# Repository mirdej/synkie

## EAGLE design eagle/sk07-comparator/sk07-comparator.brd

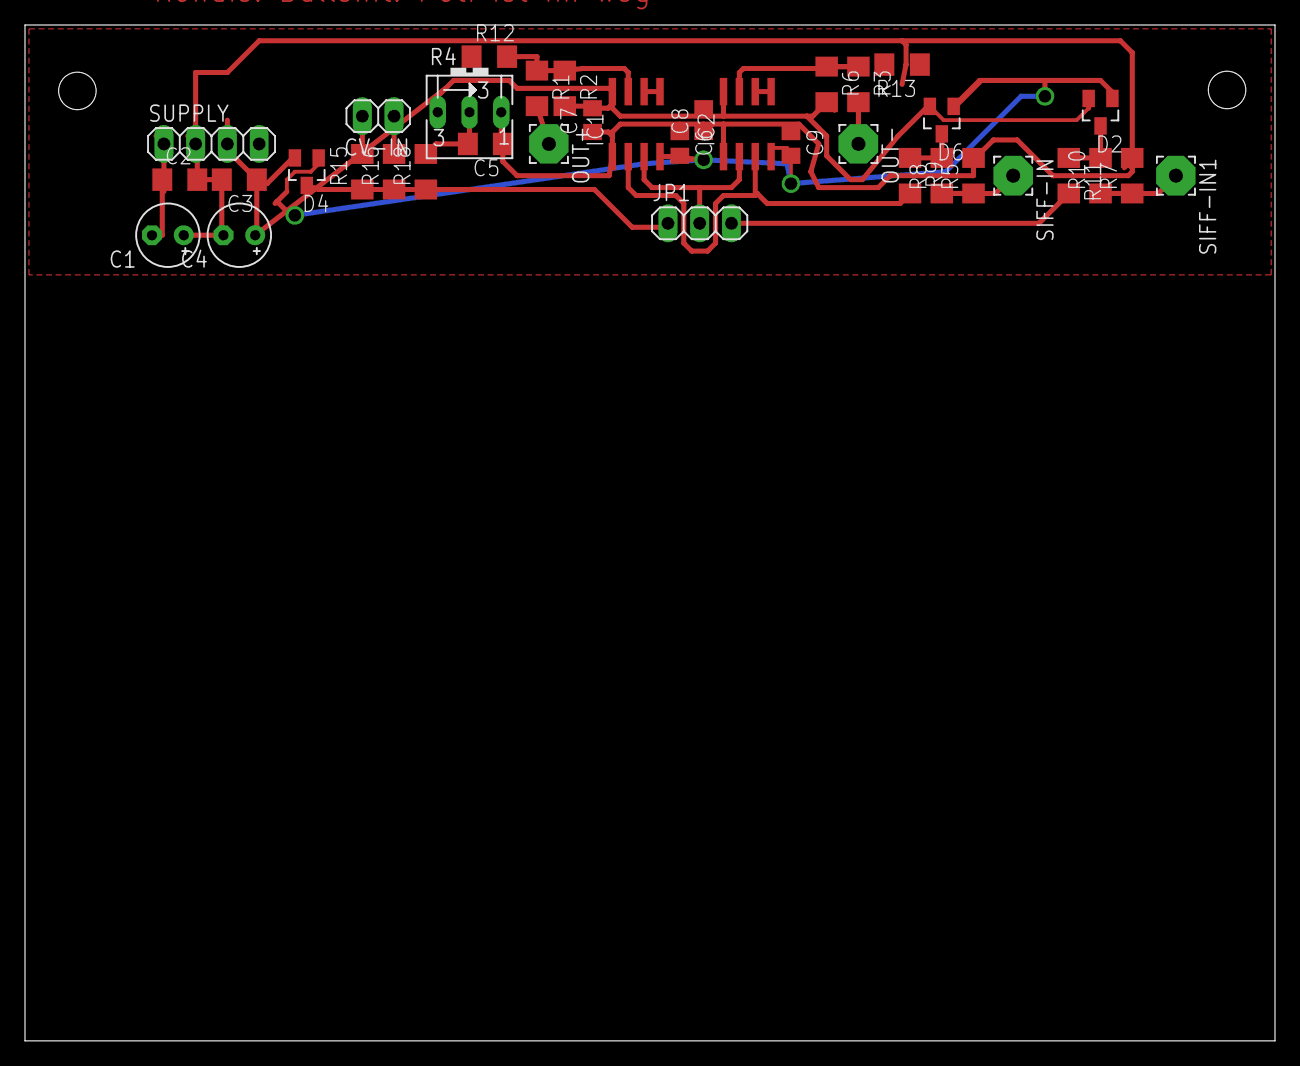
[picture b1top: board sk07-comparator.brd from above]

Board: 2 copper layers, 100.0 x 81.3 mm, 37 parts (0 on the bottom side), 20 nets.

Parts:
C1, C4: E2,5-5
C2, C3: 100n; C1206
C5: C1206
C6, C7, C8, C9: 100n; C0805
CV-IN: 1X02
D2, D4, D6: BAT54S-L44; SOT23
IC1, IC2: LM311D; SO08
JP1: 1X03
OUT+: 3,17/1,1
OUT-: 3,17/1,1
R1, R3: 75; R1206
R2, R6, R15, R16, R18: 15k; R1206
R4: B25V
R5, R7: 4k7; R1206
R8, R9, R10, R11: 100; R1206
R12, R13: 10k; R1206
SIFF-IN, SIFF-IN1: 3,17/1,1
SUPPLY: 1X04

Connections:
+5V: C3.1, C4.+, C7.2, C8.2, D2.2, D4.2, D6.2, IC1.8, IC2.8, R2.2, R4.E, R6.2, SUPPLY.3
-5V: C1.-, C2.1, C6.2, C9.2, D2.1, D4.1, D6.1, IC1.4, IC2.4, SUPPLY.1
AGND: C1.+, C2.2, C3.2, C4.-, C5.1, C6.1, C7.1, C8.1, C9.1, IC1.1, IC2.1, R4.A, R5.2, R7.2, R12.1, R13.1, SUPPLY.2
unnamed: OUT-.1, R3.2
unnamed: IC1.3, IC2.2, JP1.2
unnamed: OUT+.1, R1.2
unnamed: IC1.2, IC2.3, R9.2
unnamed: IC1.7, R1.1, R2.1, R12.2
unnamed: IC1.5, IC1.6
unnamed: IC2.7, R3.1, R6.1, R13.2
unnamed: IC2.5, IC2.6
unnamed: R7.1, R10.1, SIFF-IN1.1
unnamed: D2.3, R10.2, R11.1
unnamed: JP1.3, R11.2
unnamed: D4.3, JP1.1, R15.1, R16.1, R18.1
unnamed: R5.1, R8.1, SIFF-IN.1
unnamed: D6.3, R8.2, R9.1
unnamed: CV-IN.2, R15.2
unnamed: CV-IN.1, R16.2
unnamed: C5.2, R4.S, R18.2

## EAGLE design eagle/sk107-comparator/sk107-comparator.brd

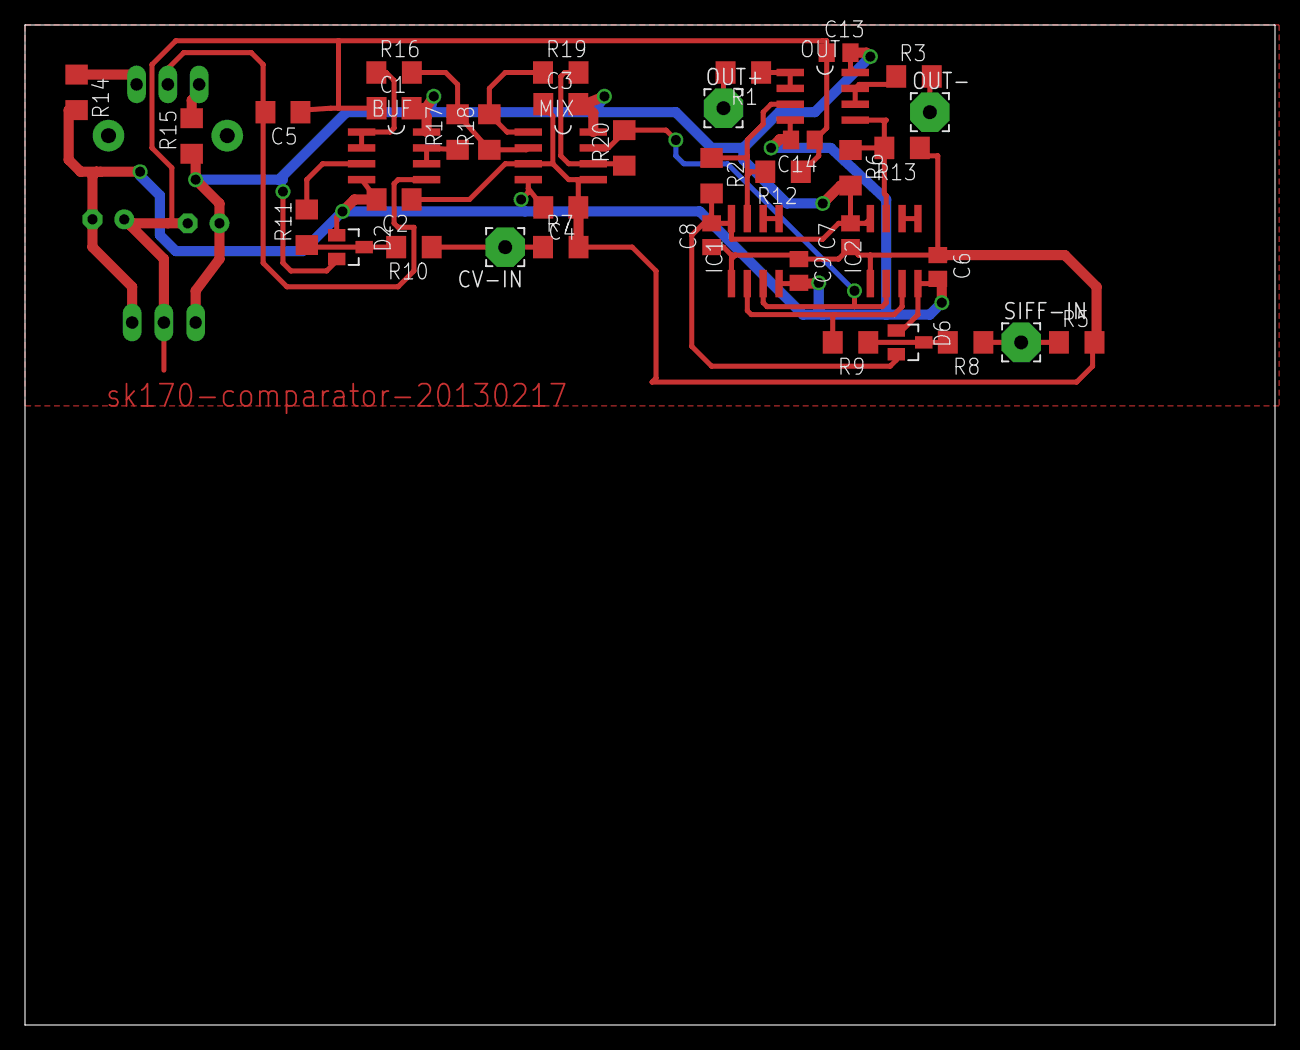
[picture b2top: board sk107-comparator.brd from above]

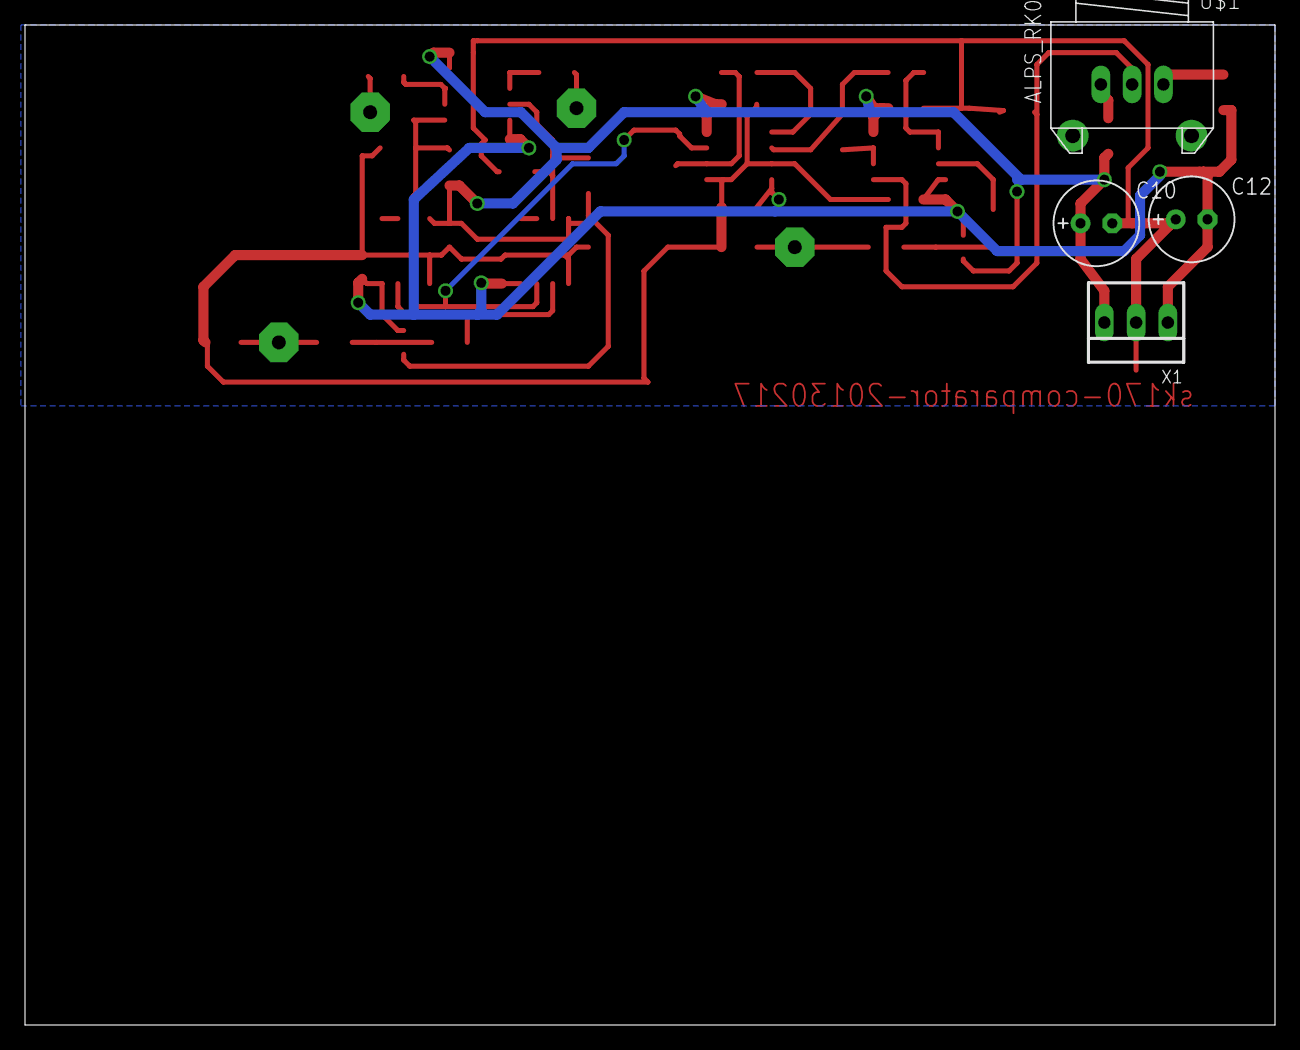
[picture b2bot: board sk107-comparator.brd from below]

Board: 2 copper layers, 100.0 x 80.0 mm, 45 parts (4 on the bottom side), 26 nets.

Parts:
BUF: MAX4392ESA; SO08
C1, C2, C3, C4, C5: C1206
C6, C7, C8, C9, C13, C14: 100n; C0805
C10, C12: E2,5-7
CV-IN: 3,17/1,1
D2, D6: BAT54S-L44; SOT23
IC1, IC2: LM311D; SO08
MIX: MAX4392ESA; SO08
OUT: MAX4392ESA; SO08
OUT+: 3,17/1,1
OUT-: 3,17/1,1
R1, R3: 75; R1206
R2, R6, R16, R17, R18, R19, R20: 6k8; R1206
R5, R7: 47k; R1206
R8, R9, R10, R11: 100; R1206
R12, R13: 1k8; R1206
R14, R15: 20k; R1206
SIFF-IN: 3,17/1,1
U$1: ALPS_RK09K111_H09L1120; ALPS_RK09L1120
X1: 22-23-2031

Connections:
+5V: BUF.8, C1.2, C3.2, C7.2, C8.2, C10.+, C13.2, D2.2, D6.2, IC1.8, IC2.8, MIX.8, OUT.8, R2.2, R6.2, R15.1, X1.3
-5V: BUF.4, C2.2, C4.2, C6.2, C9.2, C12.-, C14.2, D2.1, D6.1, IC1.4, IC2.4, MIX.4, OUT.4, R14.2, X1.1
GND: C1.1, C2.1, C3.1, C4.1, C5.1, C6.1, C7.1, C8.1, C9.1, C10.-, C12.+, C13.1, C14.1, IC1.1, IC2.1, MIX.3, MIX.5, R5.2, R7.2, R12.1, R13.1, X1.2
unnamed: BUF.5, C5.2, U$1.2
unnamed: R14.1, U$1.1
unnamed: R15.2, U$1.3
unnamed: OUT+.1, R1.2
unnamed: IC1.2, IC2.3, R9.2
unnamed: IC1.7, OUT.3, R2.1, R12.2
unnamed: IC1.5, IC1.6
unnamed: OUT.1, OUT.2, R1.1
unnamed: OUT-.1, R3.2
unnamed: CV-IN.1, R7.1, R10.1
unnamed: D2.3, R10.2, R11.1
unnamed: IC2.7, OUT.5, R6.1, R13.2
unnamed: BUF.6, BUF.7, R17.1
unnamed: BUF.3, R11.2
unnamed: R5.1, R8.1, SIFF-IN.1
unnamed: D6.3, R8.2, R9.1
unnamed: BUF.1, BUF.2, R16.1
unnamed: IC2.5, IC2.6
unnamed: MIX.2, R16.2, R17.2, R18.1
unnamed: MIX.1, R18.2, R19.1
unnamed: MIX.6, R19.2, R20.1
unnamed: IC1.3, IC2.2, MIX.7, R20.2
unnamed: OUT.6, OUT.7, R3.1

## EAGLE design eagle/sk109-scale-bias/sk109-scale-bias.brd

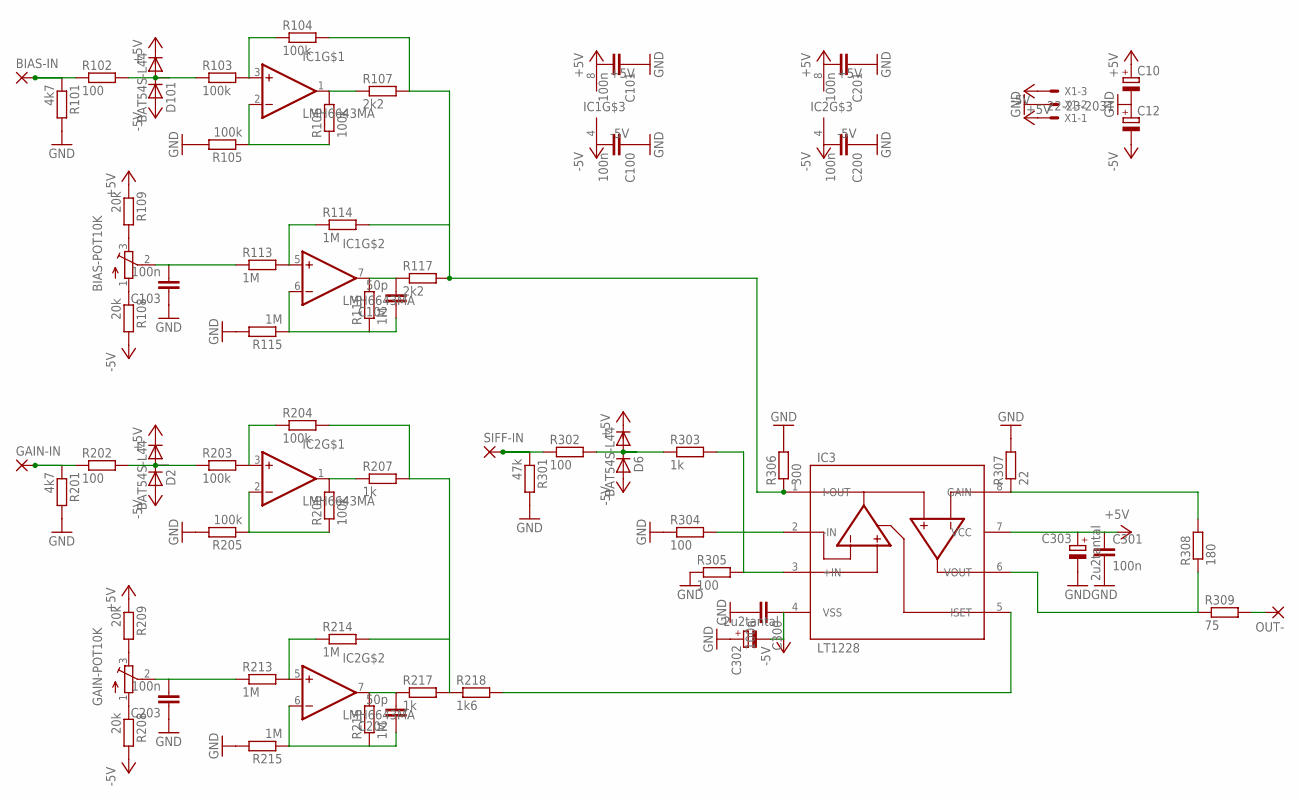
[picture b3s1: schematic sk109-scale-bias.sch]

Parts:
BIAS-IN: 3,17/1,1
BIAS-POT10K: 10k; ALPS_RK09L1120
C10, C12: CPOL-EUCT6032; CT6032
C100, C101, C103, C200, C201, C203, C300, C301: 100n; C1206
C102, C202: 50p; C1206
C302, C303: 2u2tantal; CT6032
D2, D6, D101: BAT54S-L44; SOT23
GAIN-IN: 3,17/1,1
GAIN-POT10K: 10k; ALPS_RK09L1120
IC1, IC2: LMH6643MA; SO08
IC3: LT1228; SO08
OUT-: 3,17/1,1
R101, R201: 4k7; R1206
R102, R202, R302, R304, R305: 100; R1206
R103, R104, R105, R106, R203, R204, R205, R206: 100k; R1206
R107, R117: 2k2; R1206
R108, R109, R208, R209: 20k; R1206
R113, R114, R115, R116, R213, R214, R215, R216: 1M; R1206
R207, R217, R303: 1k; R1206
R218: 1k6; R1206
R301: 47k; R1206
R306: 300; R1206
R307: 22; R1206
R308: 180; R1206
R309: 75; R1206
SIFF-IN: 3,17/1,1
X1: 22-23-2031

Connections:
+5V: C10.+, C101.2, C201.2, C301.1, C303.+, D2.2 (C), D6.2 (C), D101.2 (C), IC1.8 (+5V), IC2.8 (+5V), IC3.7 (VCC), R109.1, R209.1, X1.3
-5V: C12.-, C100.2, C200.2, C300.1, C302.-, D2.1 (A), D6.1 (A), D101.1 (A), IC1.4 (-5V), IC2.4 (-5V), IC3.4 (VSS), R108.2, R208.2, X1.1
D201: D2.3 (AC), R202.2, R203.1
D301: D6.3 (AC), R302.2, R303.1
GND: C10.-, C12.+, C100.1, C101.1, C103.1, C200.1, C201.1, C203.1, C300.2, C301.2, C302.+, C303.-, R101.2, R105.2, R115.2, R201.2, R205.2, R215.2, R301.2, R304.1, R305.1, R306.2, R307.2, X1.2
unnamed: C203.2, GAIN-POT10K.2 (W), R213.1
unnamed: GAIN-POT10K.1 (S), R208.1
unnamed: GAIN-POT10K.3 (E), R209.2
unnamed: IC2.2 (-IN), R205.1, R206.1
unnamed: IC3.3 (+IN), R303.2, R305.2
unnamed: IC3.1 (I-OUT), R104.2, R107.2, R114.2, R117.2, R306.1
unnamed: IC2.5 (+IN), R213.2, R214.1
unnamed: C202.2, IC2.7 (OUT), R216.2, R217.1
unnamed: IC3.8 (GAIN), R307.1, R308.2
unnamed: GAIN-IN.1, R201.1, R202.1
unnamed: C202.1, IC2.6 (-IN), R215.1, R216.1
unnamed: BIAS-IN.1, R101.1, R102.1
unnamed: IC2.3 (+IN), R203.2, R204.1
unnamed: R301.1, R302.1, SIFF-IN.1
unnamed: IC2.1 (OUT), R206.2, R207.1
unnamed: IC3.5 (ISET), R218.2
unnamed: R204.2, R207.2, R214.2, R217.2, R218.1
unnamed: IC3.6 (VOUT), R308.1, R309.1
unnamed: OUT-.1, R309.2
unnamed: IC3.2 (-IN), R304.2
unnamed: D101.3 (AC), R102.2, R103.1
unnamed: IC1.3 (+IN), R103.2, R104.1
unnamed: IC1.1 (OUT), R106.2, R107.1
unnamed: BIAS-POT10K.2 (W), C103.2, R113.1
unnamed: BIAS-POT10K.1 (S), R108.1
unnamed: BIAS-POT10K.3 (E), R109.2
unnamed: IC1.5 (+IN), R113.2, R114.1
unnamed: C102.2, IC1.7 (OUT), R116.2, R117.1
unnamed: C102.1, IC1.6 (-IN), R115.1, R116.1
R105: IC1.2 (-IN), R105.1, R106.1

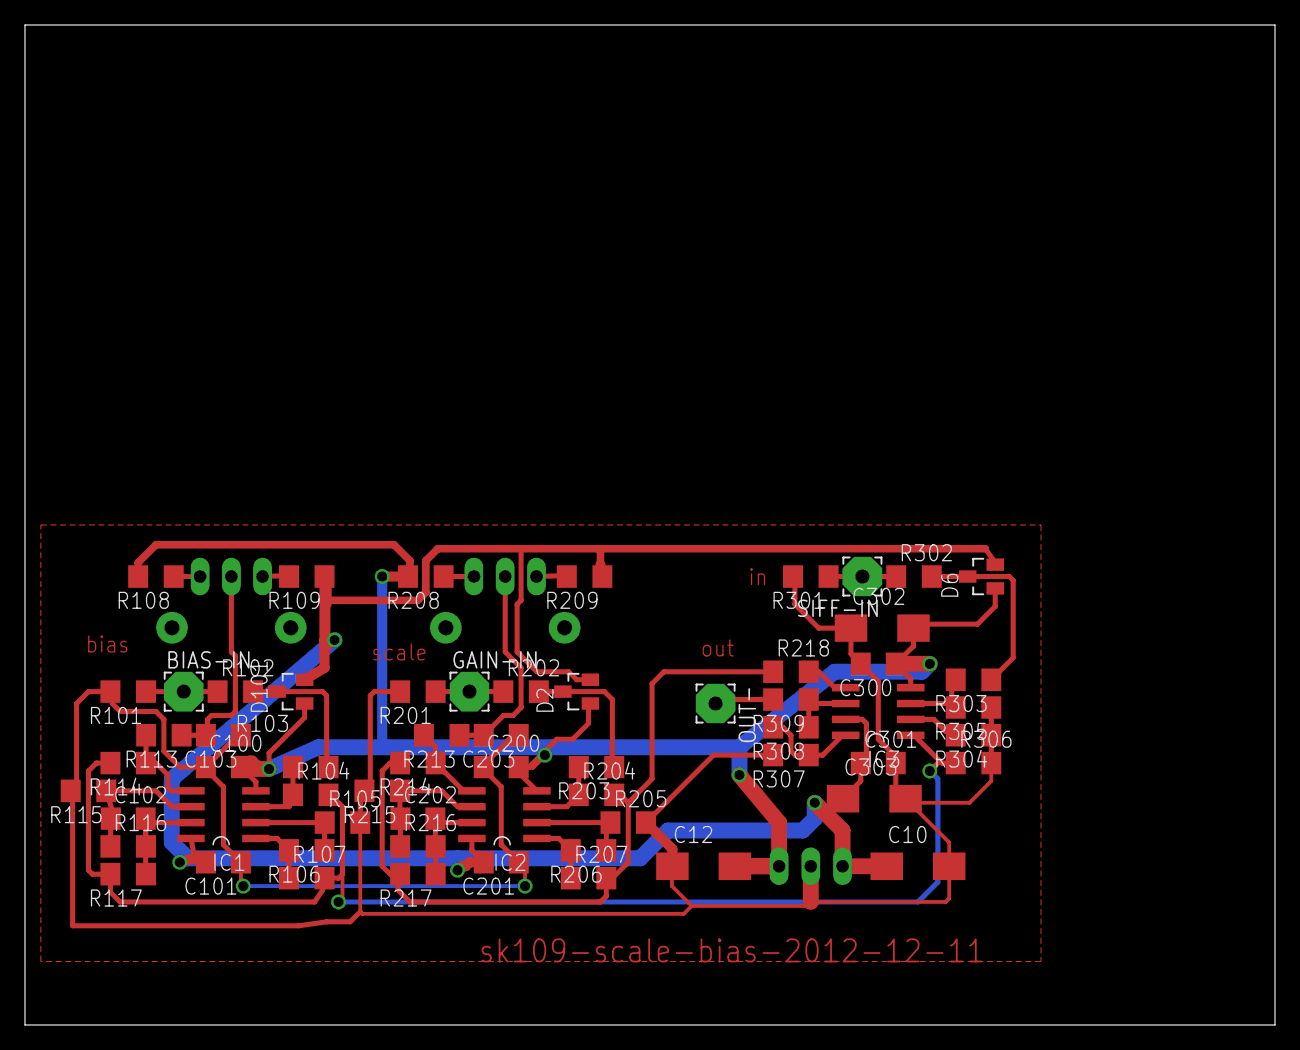
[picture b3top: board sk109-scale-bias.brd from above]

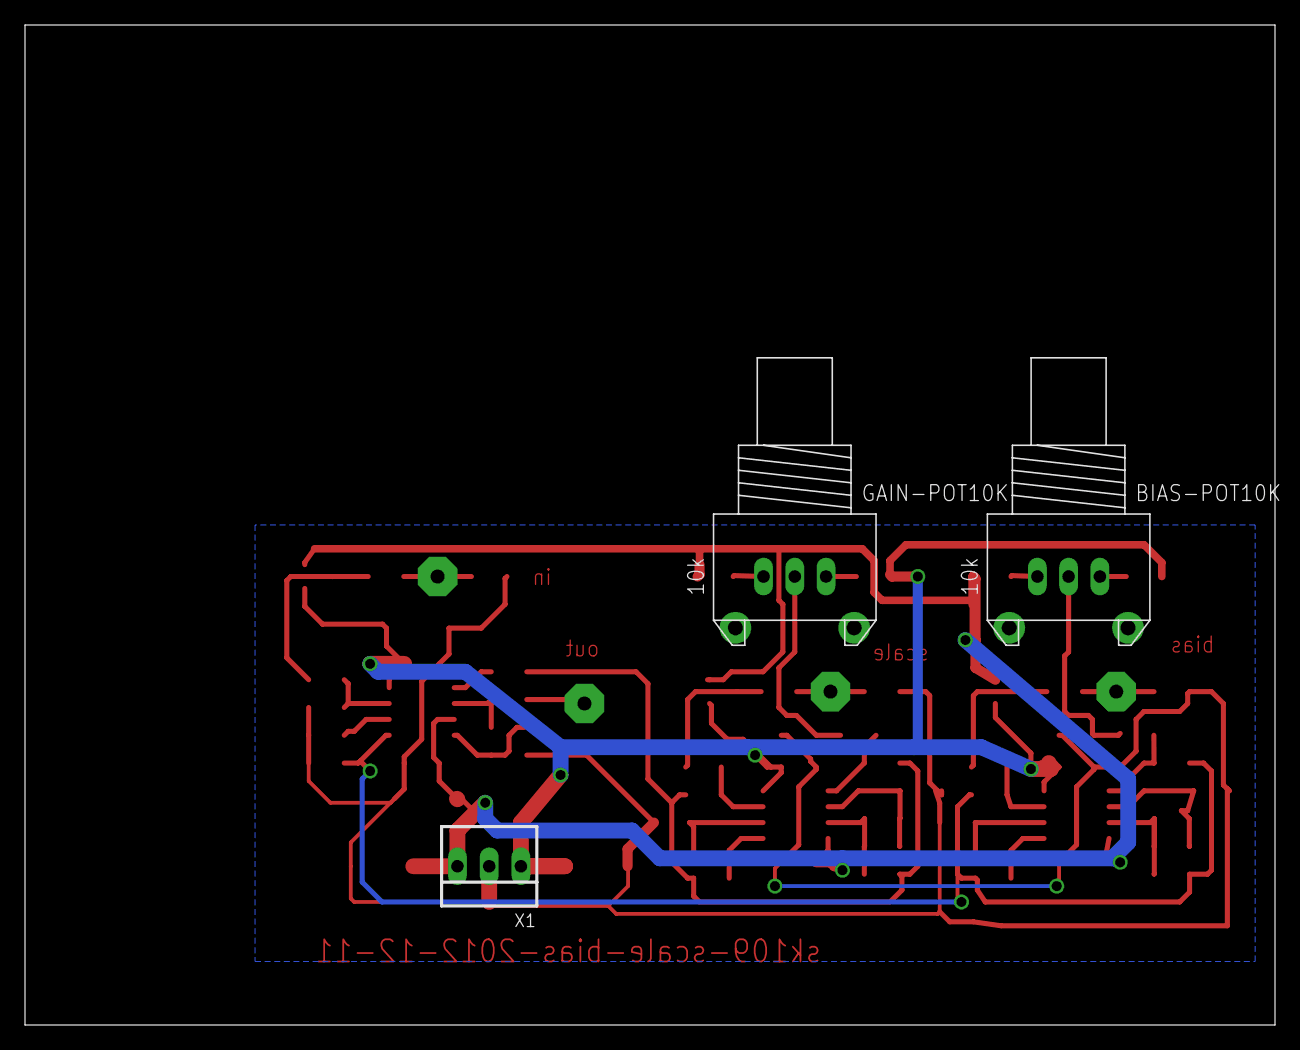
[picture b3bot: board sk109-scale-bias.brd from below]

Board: 2 copper layers, 100.0 x 80.0 mm, 65 parts (3 on the bottom side), 35 nets.

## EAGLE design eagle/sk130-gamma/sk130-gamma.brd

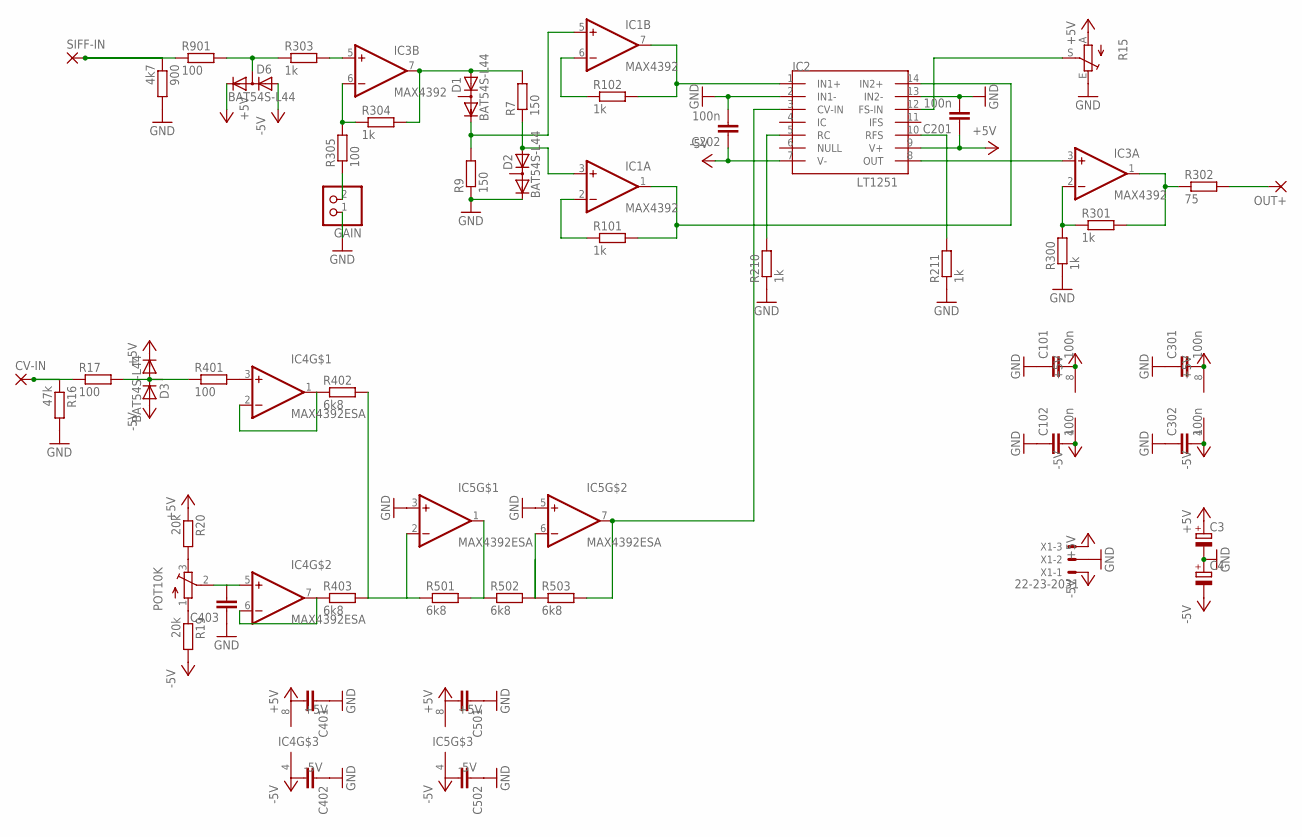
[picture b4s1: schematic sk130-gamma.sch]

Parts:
900: 4k7; R1206
C3, C4: CPOL-EUCT6032; CT6032
C101, C102, C201, C202, C301, C302: 100n; C1206
C401, C402, C403, C501, C502: C-EUC1206; C1206
CV-IN: 3,17/1,1
D1, D2, D3, D6: BAT54S-L44; SOT23
GAIN: PINHD-1X2; 1X02
IC1, IC3: MAX4392; SO08
IC2: LT1251; SO14
IC4, IC5: MAX4392ESA; SO08
OUT+: 3,17/1,1
POT10K: 10k; ALPS_RK09K111_H
R7, R9: 150; R1206
R15: TRIM_EU-B64W; B64W
R16: 47k; R1206
R17, R305, R401, R901: 100; R1206
R19, R20: 20k; R1206
R101, R102, R210, R211, R300, R301, R303, R304: 1k; R1206
R302: 75; R1206
R402, R403, R501, R502, R503: 6k8; R1206
SIFF-IN: 3,17/1,1
X1: 22-23-2031

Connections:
+5V: C3.+, C101.2, C201.1, C301.2, C401.2, C501.2, D3.2 (C), D6.2 (C), IC1.8 (V+), IC2.9 (V+), IC3.8 (V+), IC4.8 (+5V), IC5.8 (+5V), R15.A, R20.1, X1.3
-5V: C4.-, C102.2, C202.1, C302.2, C402.2, C502.2, D3.1 (A), D6.1 (A), IC1.4 (V-), IC2.7 (V-), IC3.4 (V-), IC4.4 (-5V), IC5.4 (-5V), R19.2, X1.1
GND: 900.2, C3.-, C4.+, C101.1, C102.1, C201.2, C202.2, C301.1, C302.1, C401.1, C402.1, C403.1, C501.1, C502.1, D2.2 (C), GAIN.1, IC2.2 (IN1-), IC2.13 (IN2-), IC5.3 (+IN), IC5.5 (+IN), R9.1, R15.E, R16.2, R210.1, R211.1, R300.1, X1.2
unnamed: IC3.6 (-IN), R304.1, R305.2
unnamed: IC3.5 (+IN), R303.2
unnamed: OUT+.1, R302.2
unnamed: IC2.8 (OUT), IC3.3 (+IN)
unnamed: D1.1 (A), IC3.7 (OUT), R7.2, R304.2
unnamed: GAIN.2, R305.1
unnamed: IC3.2 (-IN), R300.2, R301.1
unnamed: IC3.1 (OUT), R301.2, R302.1
unnamed: D1.2 (C), IC1.5 (+IN), R9.2
unnamed: IC2.5 (RC), R210.2
unnamed: D2.1 (A), IC1.3 (+IN), R7.1
unnamed: IC2.10 (RFS), R211.2
unnamed: IC1.2 (-IN), R101.1
unnamed: 900.1, R901.1, SIFF-IN.1
unnamed: D6.3 (AC), R303.1, R901.2
unnamed: IC1.6 (-IN), R102.1
unnamed: IC1.1 (OUT), IC2.14 (IN2+), R101.2
unnamed: IC2.12 (FS-IN), R15.S
unnamed: CV-IN.1, R16.1, R17.1
unnamed: D3.3 (AC), R17.2, R401.1
unnamed: IC4.3 (+IN), R401.2
unnamed: IC4.1 (OUT), IC4.2 (-IN), R402.1
unnamed: IC4.6 (-IN), IC4.7 (OUT), R403.1
unnamed: IC5.2 (-IN), R402.2, R403.2, R501.1
unnamed: IC5.1 (OUT), R501.2, R502.1
unnamed: IC5.6 (-IN), R502.2, R503.1
unnamed: IC2.3 (CV-IN), IC5.7 (OUT), R503.2
unnamed: C403.2, IC4.5 (+IN), POT10K.2 (W)
unnamed: POT10K.1 (S), R19.1
unnamed: POT10K.3 (E), R20.2
unnamed: IC1.7 (OUT), IC2.1 (IN1+), R102.2

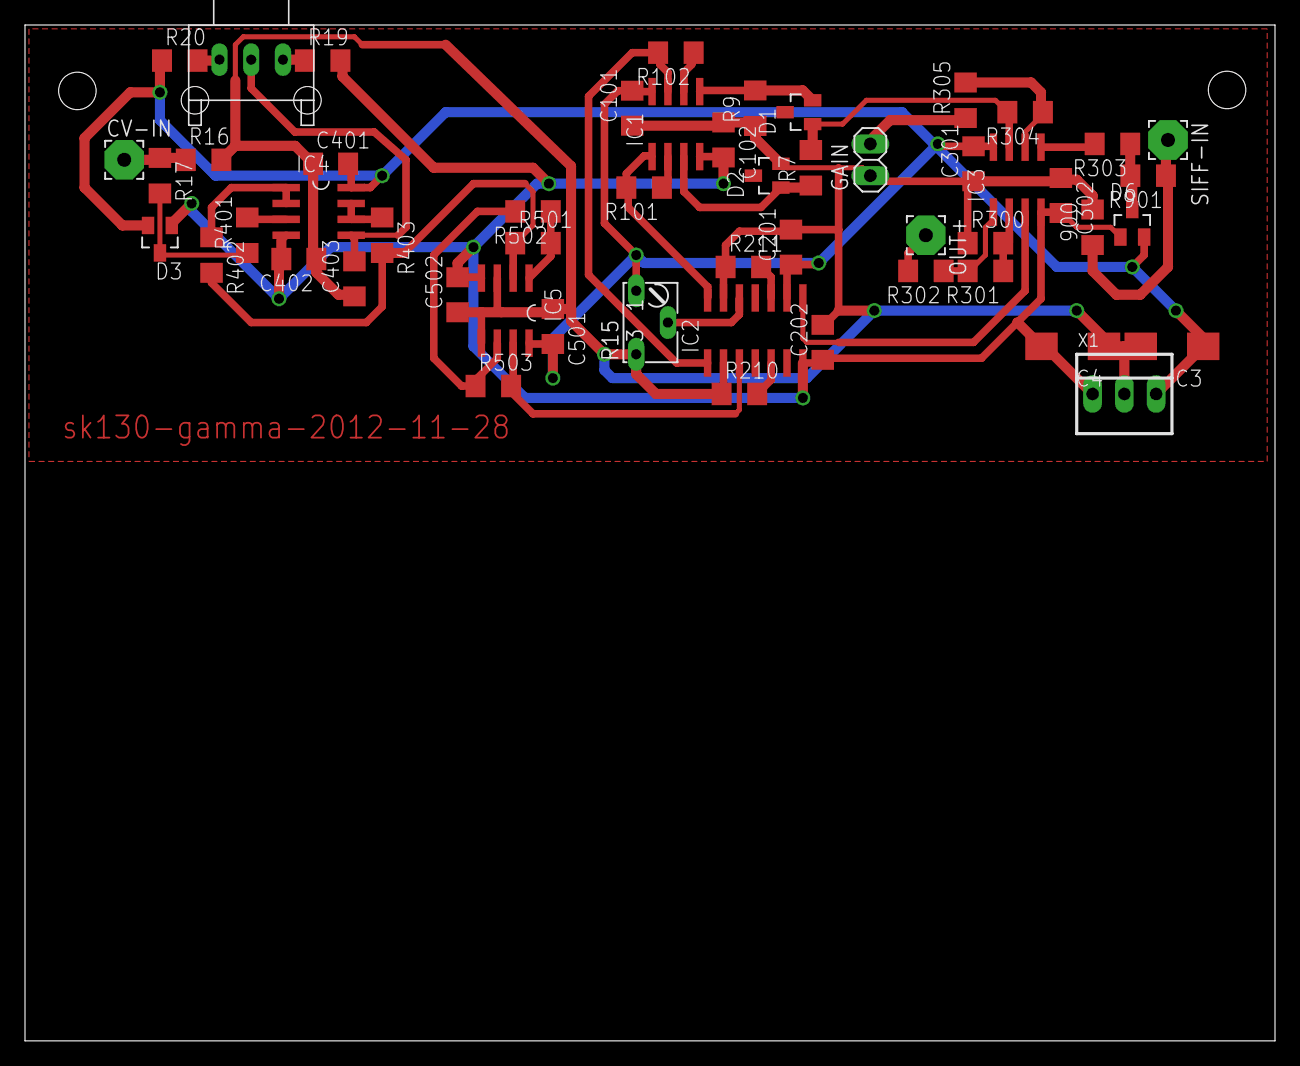
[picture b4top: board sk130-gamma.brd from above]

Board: 2 copper layers, 100.0 x 81.3 mm, 53 parts (0 on the bottom side), 34 nets.
